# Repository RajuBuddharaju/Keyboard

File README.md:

# Introduction

This is fork of <a href="https://github.com/Narkoleptika/josukey" target ="_blank">Josukey</a>. 

## Thanks

* <a href="https://github.com/ergogen/ergogen" target="_blank">Ergogen</a>
* <a href="https://discord.gg/nbKcAZB" target="_blank">Absolem Club Discord</a>
* <a href="https://github.com/tsteffek/Ergogen-V4-Migration-Guide" target="_blank">V4 Migration Guide</a>
* <a href="https://gitlab.com/Audijo/keyboard" target="_blank">Claw</a>
* <a href="https://github.com/MrCarney/mrkeyboard" target="_blank">MrKeyboard</a>
* <a href="https://github.com/foostan/crkbd" target="_blank">Corne keyboard</a>
* <a href="https://github.com/Narkoleptika/josukey" target ="_blank">Josukey</a>
* <a href="https://flatfootfox.com/ergogen-introduction/" target ="_blank">FlatFootFox</a>

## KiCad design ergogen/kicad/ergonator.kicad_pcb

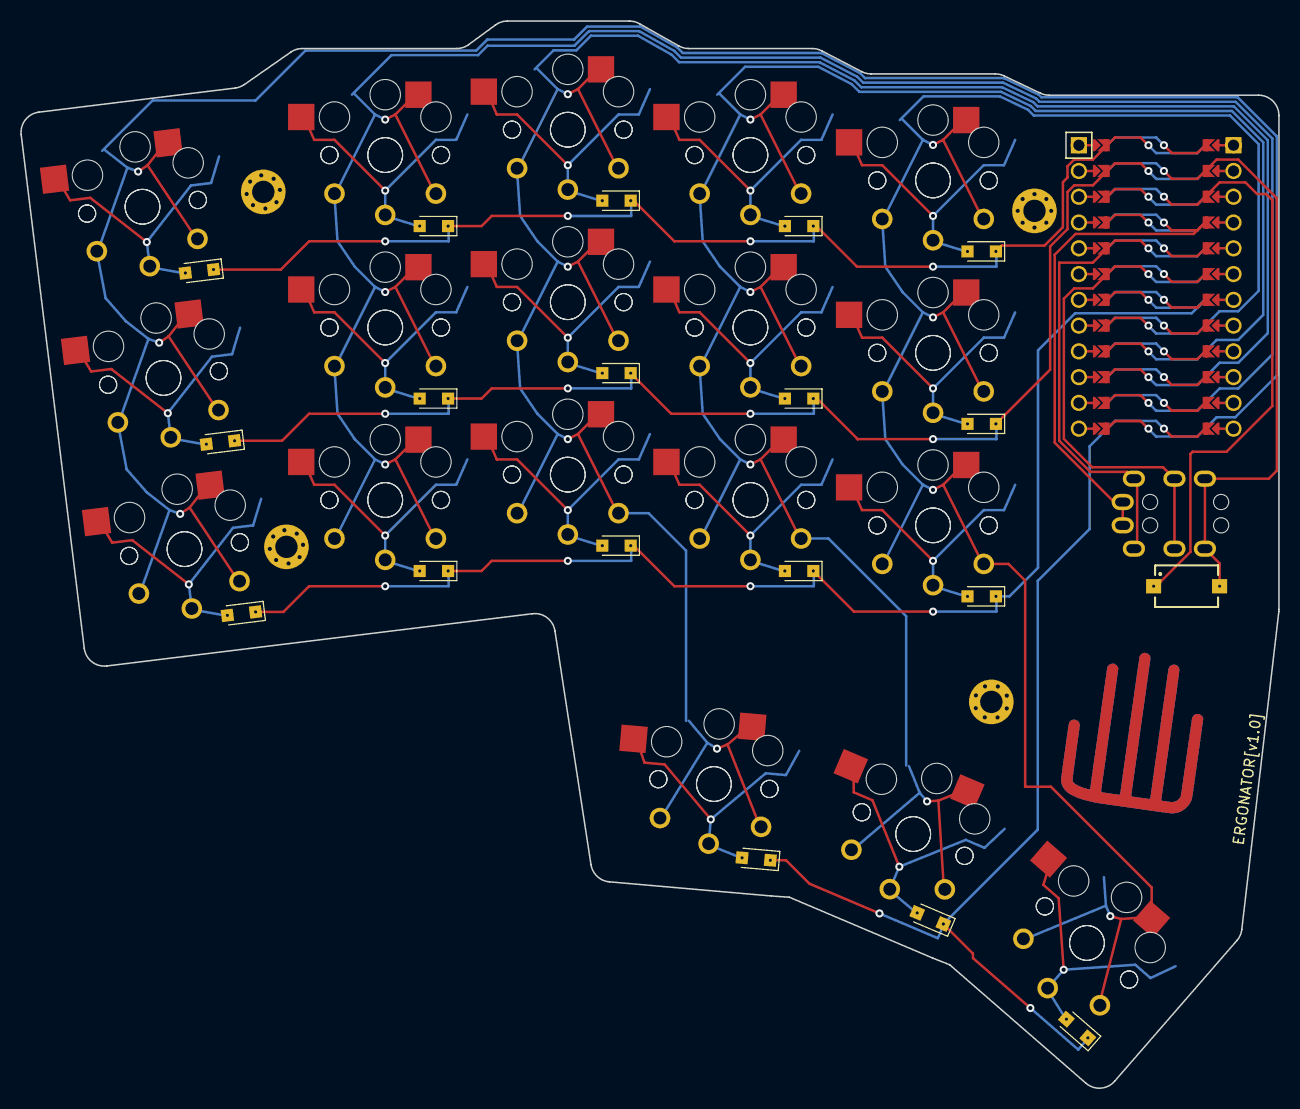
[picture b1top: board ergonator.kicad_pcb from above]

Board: 2 copper layers, 124.0 x 105.2 mm, 61 parts (0 on the bottom side), 32 nets.

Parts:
D1, D2, D3, D4, D5, D6, D7, D8, D9, D10, D11, D12, D13, D14, D15, D16, D17, D18: Nexperia_CFP3_SOD-123W
MCU1: ProMicro
S1, S2, S3, S4, S5, S6, S7, S8, S9, S10, S11, S12, S13, S14, S15, S16, S17, S18, S19, S20, S21, S22, S23, S24, S25, S26, S27, S28, S29, S30, S31, S32, S33, S34, S35, S36: PG1350
S37: 434121025816
TRRS1: TRRS-PJ-320A-dual
_195, _196, _197, _198: MountingHole_2.2mm_M2_Pad_Via

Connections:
GND: MCU1.2, MCU1.21, MCU1.22, S37.2, TRRS1.4
P0: D2.1, D5.1, D8.1, D11.1, D14.1, MCU1.23
P1: D3.1, D6.1, D9.1, D12.1, D15.1, MCU1.24
P2: MCU1.20, TRRS1.2
P3: MCU1.19, TRRS1.3
P4: D1.1, D4.1, D7.1, D10.1, D13.1, MCU1.18
P5: MCU1.17, S13.1, S14.1, S15.1, S18.1, S31.1, S32.1, S33.1, S36.1
P6: MCU1.16, S10.1, S11.1, S12.1, S17.1, S28.1, S29.1, S30.1, S35.1
P7: MCU1.15, S7.1, S8.1, S9.1, S16.1, S25.1, S26.1, S27.1, S34.1
P8: MCU1.14, S4.1, S5.1, S6.1, S22.1, S23.1, S24.1
P9: MCU1.13, S1.1, S2.1, S3.1, S19.1, S20.1, S21.1
P10: D16.1, D17.1, D18.1, MCU1.12
RST: MCU1.3, S37.1
VCC: MCU1.4, TRRS1.1
main_index_bottom: D10.2, S10.2, S28.2
main_index_home: D11.2, S11.2, S29.2
main_index_top: D12.2, S12.2, S30.2
main_inner_bottom: D13.2, S13.2, S31.2
main_inner_home: D14.2, S14.2, S32.2
main_inner_top: D15.2, S15.2, S33.2
main_middle_bottom: D7.2, S7.2, S25.2
main_middle_home: D8.2, S8.2, S26.2
main_middle_top: D9.2, S9.2, S27.2
main_pinky_bottom: D1.2, S1.2, S19.2
main_pinky_home: D2.2, S2.2, S20.2
main_pinky_top: D3.2, S3.2, S21.2
main_ring_bottom: D4.2, S4.2, S22.2
main_ring_home: D5.2, S5.2, S23.2
main_ring_top: D6.2, S6.2, S24.2
thumb_home_home: D17.2, S17.2, S35.2
thumb_inner_home: D16.2, S16.2, S34.2
thumb_outer_home: D18.2, S18.2, S36.2

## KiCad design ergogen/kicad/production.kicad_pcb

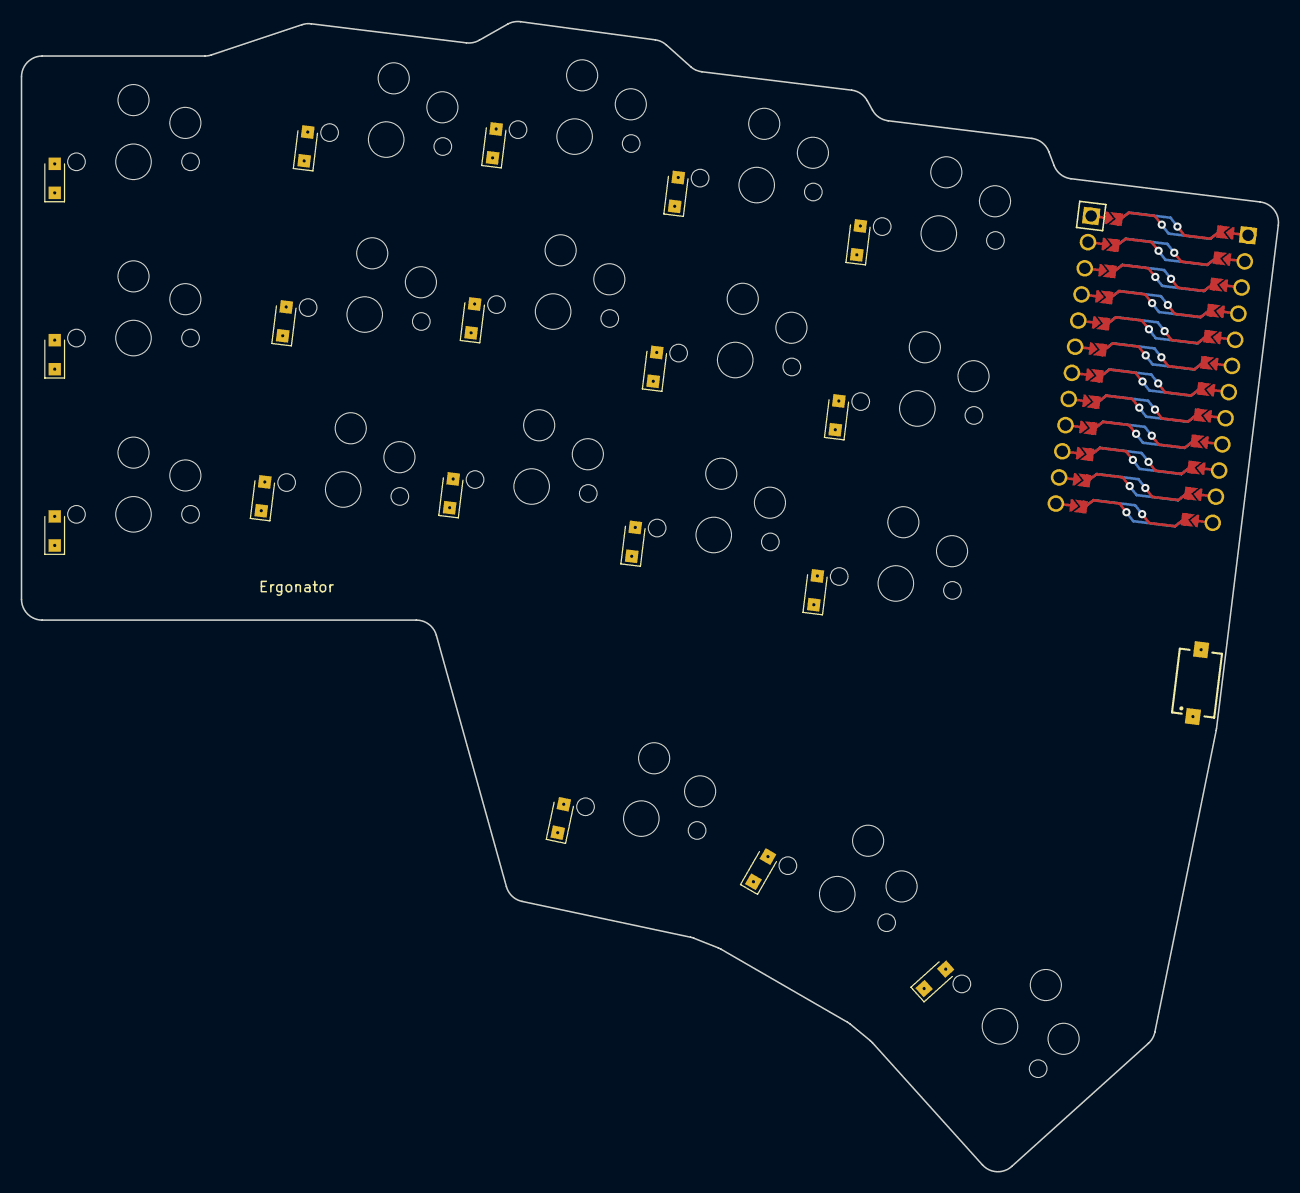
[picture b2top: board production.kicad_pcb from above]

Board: 2 copper layers, 121.2 x 110.9 mm, 38 parts (0 on the bottom side), 29 nets.

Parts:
D1, D2, D3, D4, D5, D6, D7, D8, D9, D10, D11, D12, D13, D14, D15, D16, D17, D18: Nexperia_CFP3_SOD-123W
MCU1: ProMicro
S1, S2, S3, S4, S5, S6, S7, S8, S9, S10, S11, S12, S13, S14, S15, S16, S17, S18: PG1350
S19: 434121025816

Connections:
GND: MCU1.2, MCU1.21, MCU1.22, S19.2
P0: D2.1, D5.1, D8.1, D11.1, D14.1, MCU1.23
P1: D3.1, D6.1, D9.1, D12.1, D15.1, MCU1.24
P2: D1.1, D4.1, D7.1, D10.1, D13.1, MCU1.20
P3: MCU1.19, S13.1, S14.1, S15.1, S18.1
P4: MCU1.18, S10.1, S11.1, S12.1, S17.1
P5: MCU1.17, S7.1, S8.1, S9.1, S16.1
P6: MCU1.16, S4.1, S5.1, S6.1
P7: MCU1.15, S1.1, S2.1, S3.1
P8: D16.1, D17.1, D18.1, MCU1.14
RST: MCU1.3, S19.1
main_index_bottom: D10.2, S10.2
main_index_home: D11.2, S11.2
main_index_top: D12.2, S12.2
main_inner_bottom: D13.2, S13.2
main_inner_home: D14.2, S14.2
main_inner_top: D15.2, S15.2
main_middle_bottom: D7.2, S7.2
main_middle_home: D8.2, S8.2
main_middle_top: D9.2, S9.2
main_pinky_bottom: D1.2, S1.2
main_pinky_home: D2.2, S2.2
main_pinky_top: D3.2, S3.2
main_ring_bottom: D4.2, S4.2
main_ring_home: D5.2, S5.2
main_ring_top: D6.2, S6.2
thumb_home_home: D17.2, S17.2
thumb_inner_home: D16.2, S16.2
thumb_outer_home: D18.2, S18.2

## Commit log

2024-12-12 Initial design for the Ergonator. Installed Ergogen locally.
2024-12-14 Changed stagger and added outlines.
2024-12-21 Added switch and diode footprints. Added a KiCAD project and a makefile.
2025-02-16 Refactoring and adding makefile.
2025-02-16 Added TRRS connector and changed row and column net.
2025-02-16 Wiring done.
2025-02-16 Removed all references to ZMK.
2025-02-16 Removed all josukey kicad files.
2025-04-18 Added more shiz to gitignore.
2025-05-04 Added version number on the board and started work so silkscreen art.
2025-05-05 Ergontaor[v1.0] with correct switches and complete wiring.
2025-05-05 Connected grounds on pcb.
2025-05-22 Changed trrs connector footprint and started modifying config for a case.
2025-05-28 Changed padding variables and remade board outline.
2025-05-30 Added autogenerated (inter)key routing and non-hotswapability
    With these alterations ergogen will generate a non-hotswap key on top of
    the hot swap one for better flexibility. This patch also adds basic routing
    within the key itself, and between keys with a known location. This reduces
    the amount of wiring that needs to be done and keeps the look of each key
    the same.
2025-07-04 Added firmware with all the layers I need so far and started on the case.
    One caveat is that the config should think if the keys as mirrored for some reason and I don't know why.
